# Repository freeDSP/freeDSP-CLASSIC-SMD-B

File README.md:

# freeDSP CLASSIC SMD

SMD update of the freeDSP CLASSIC.

**BOARD STATUS:** ✅ READY TO BE BUILT

## About

The freeDSP is an open-source digital signal processor family for the do-it-yourself community. The applications range from active loudspeaker concepts (digital crossovers, bass enhancement, ...) and room equalization over advanced musical effect processors to car audio signal processing.

This _freeDSP Classic SMD-B_ is a updated SMD version of the original _freeDSP Classic_ with a few improvements/changes.

This board has been designed using the Cross-Platform Open Source Tool [KiCad](http://kicad.org/).

More information can be found on the [freeDSP website](http://freedsp.cc)

You can find a PDF version of the schematic in the SOURCES folder (freeDSP_Classic_SMD.pdf)

## Links

### FreeDSP

Website: [http://freedsp.cc/](http://freedsp.cc)
FreeDSP Guidelines: [freedsp wiki - freeDSP-Guidelines](https://github.com/freeDSP/WIKI-AND-GENERAL-TOPICS/wiki/freeDSP-Guidelines)

### Documentation

[Getting Started (Google Doc)](https://docs.google.com/document/d/1K3joEg4iIRMazfqGLaVoBdybitr4o_KIVZfQ-qeNDzs/preview)  
[Getting Started (PDF Download)](https://docs.google.com/document/d/1K3joEg4iIRMazfqGLaVoBdybitr4o_KIVZfQ-qeNDzs/export?format=pdf)  

[Schematic (PDF)](./SOURCES/freeDSP_Classic_SMD.pdf)  
[Bill Of Materials (CSV)](./GERBER/freeDSP_Classic_SMD_BOM.csv)

## Git usage

### How to setup local repository

1. Change to your FreeDSP directory. This may be any directory you'd like to clone the repository to.
2. Clone the repository (including submodule)  
   `git clone --recursive https://github.com/freeDSP/freeDSP-CLASSIC-SMD-B.git`
3. Change to the newly created Classic-SMD-B directory
4. Checkout a branch for the library submodule, if you want to modify it as well  
   `git submodule foreach 'git checkout 'master''`
5. Open the project file in KiCad

**❔Note:** If you (accidentally) clone the repository without `--recursive`, initialise the `freeDSP/freeDSP-KiCadLibrary` submodule with `git submodule init ./LIBRARY`.

### Updating your local copy

1. To update the project  
   `git pull`
2. To update the library  
   `git submodule update --remote --merge`

### Committing and pushing local changes

This step requires you to have push access to the repository. If you do not have this, [create a fork](https://docs.github.com/en/get-started/quickstart/fork-a-repo#about-forks).

For ease of development, please use a separate branch (on your fork) to propose changes:

1. Create a new branch: git branch newfeature.
2. Checkout new branch: (this will not reset your work.) git checkout newfeature.

Then, continue to commit your changes:

1. If you modified something in the LIBRARY folder, change to the LIBRARY folder and run  
   `git add .` (Only required if files were added)  
   `git commit -am "Message"`  (Describe what you changed)  
2. Change to the project root directory and run
   `git add .` (Only required if files were added)  
   `git commit -am "Message"`  (Describe what you changed)  
3. In the project directory, run  
   `git push --recurse-submodule=on-demand`  

### Suggesting changes

To suggest changes from your fork and/or branch to [freeDSP][]/[freeDSP-CLASSIC-SMD-B][], follow the instructions that apply to you.

From a fork repository (outside contributors):

1. Navigate to the `Pull requests` page of your fork, and click "New pull request"
2. Review the changes in the differential below. Ideally, there are no merge conflicts, and you are "✅ Able to merge".  
   If you see no changes or differential, follow the steps outlined for the project contributors below.  
   if there are any merge conflicts, resolve these. See [Contributing to projects][docs-contrib] for more help.
3. Click "Create pull request" and enter
   - **Title** describing your suggestion briefly
   - **Comment** describing your suggestions one-by-one, or more in-depth
4. Click "Create pull request" once again. Your pull request will now be made.

From the main repository (for project contributors):

1. Navigate to the [pull requests][freedsp-pulls] page and click "New pull request"
2. Click "compare across forks" immediately below "Compare changes" if necessary.
3. Create a new pull request
   - select "master" as "base:"
   - select your branch on your fork as "compare:"
4. Review the changes in the differential below. Ideally, there are no merge conflicts, and you are "✅ Able to merge".  
   If there are any merge conflicts, resolve these. See [Contributing to projects][docs-contrib] for more help.
5. Click "Create pull request" and enter
   - **Title** describing your suggestion briefly
   - **Comment** describing your suggestions one-by-one, or more in-depth
6. Click "Create pull request" once again. Your pull request will now be made.

### Define alias to make things shorter (optional)

Change to the project root and run  

`git config alias.supdate 'submodule update --remote --merge'`  
`git config alias.spush 'push --recurse-submodules=on-demand'`  

Afterwards, you can use `git supdate` to update the submodule and `git spush` to push any commited changes  

### Other useful commands

`git status`  
Shows general information about the current branch, uncommited changes, not yet added new files and more

`git diff`  
Shows uncommited changes

`git reset --hard origin/master`  
Resets all files to the current status of the dev-hs-01 branch on the Github repository  
  **⚠️ Warning** - This deletes all local changes, so make sure all changes you made and you do not want to delete are pushed to the remote repository

## License

[Creative Commons Attribution Share-Alike 4.0 license](https://creativecommons.org/licenses/by-sa/4.0/)  
[Local license file](./LICENCE)

2019 ©️ [FreeDSP project](http://freedsp.cc)

[freeDSP]: https://github.com/freeDSP
[freeDSP-CLASSIC-SMD-B]: https://github.com/freeDSP/freeDSP-CLASSIC-SMD-B
[docs-contrib]:https://docs.github.com/en/get-started/quickstart/contributing-to-projects
[freedsp-pulls]:https://github.com/freeDSP/freeDSP-CLASSIC-SMD-B/pulls

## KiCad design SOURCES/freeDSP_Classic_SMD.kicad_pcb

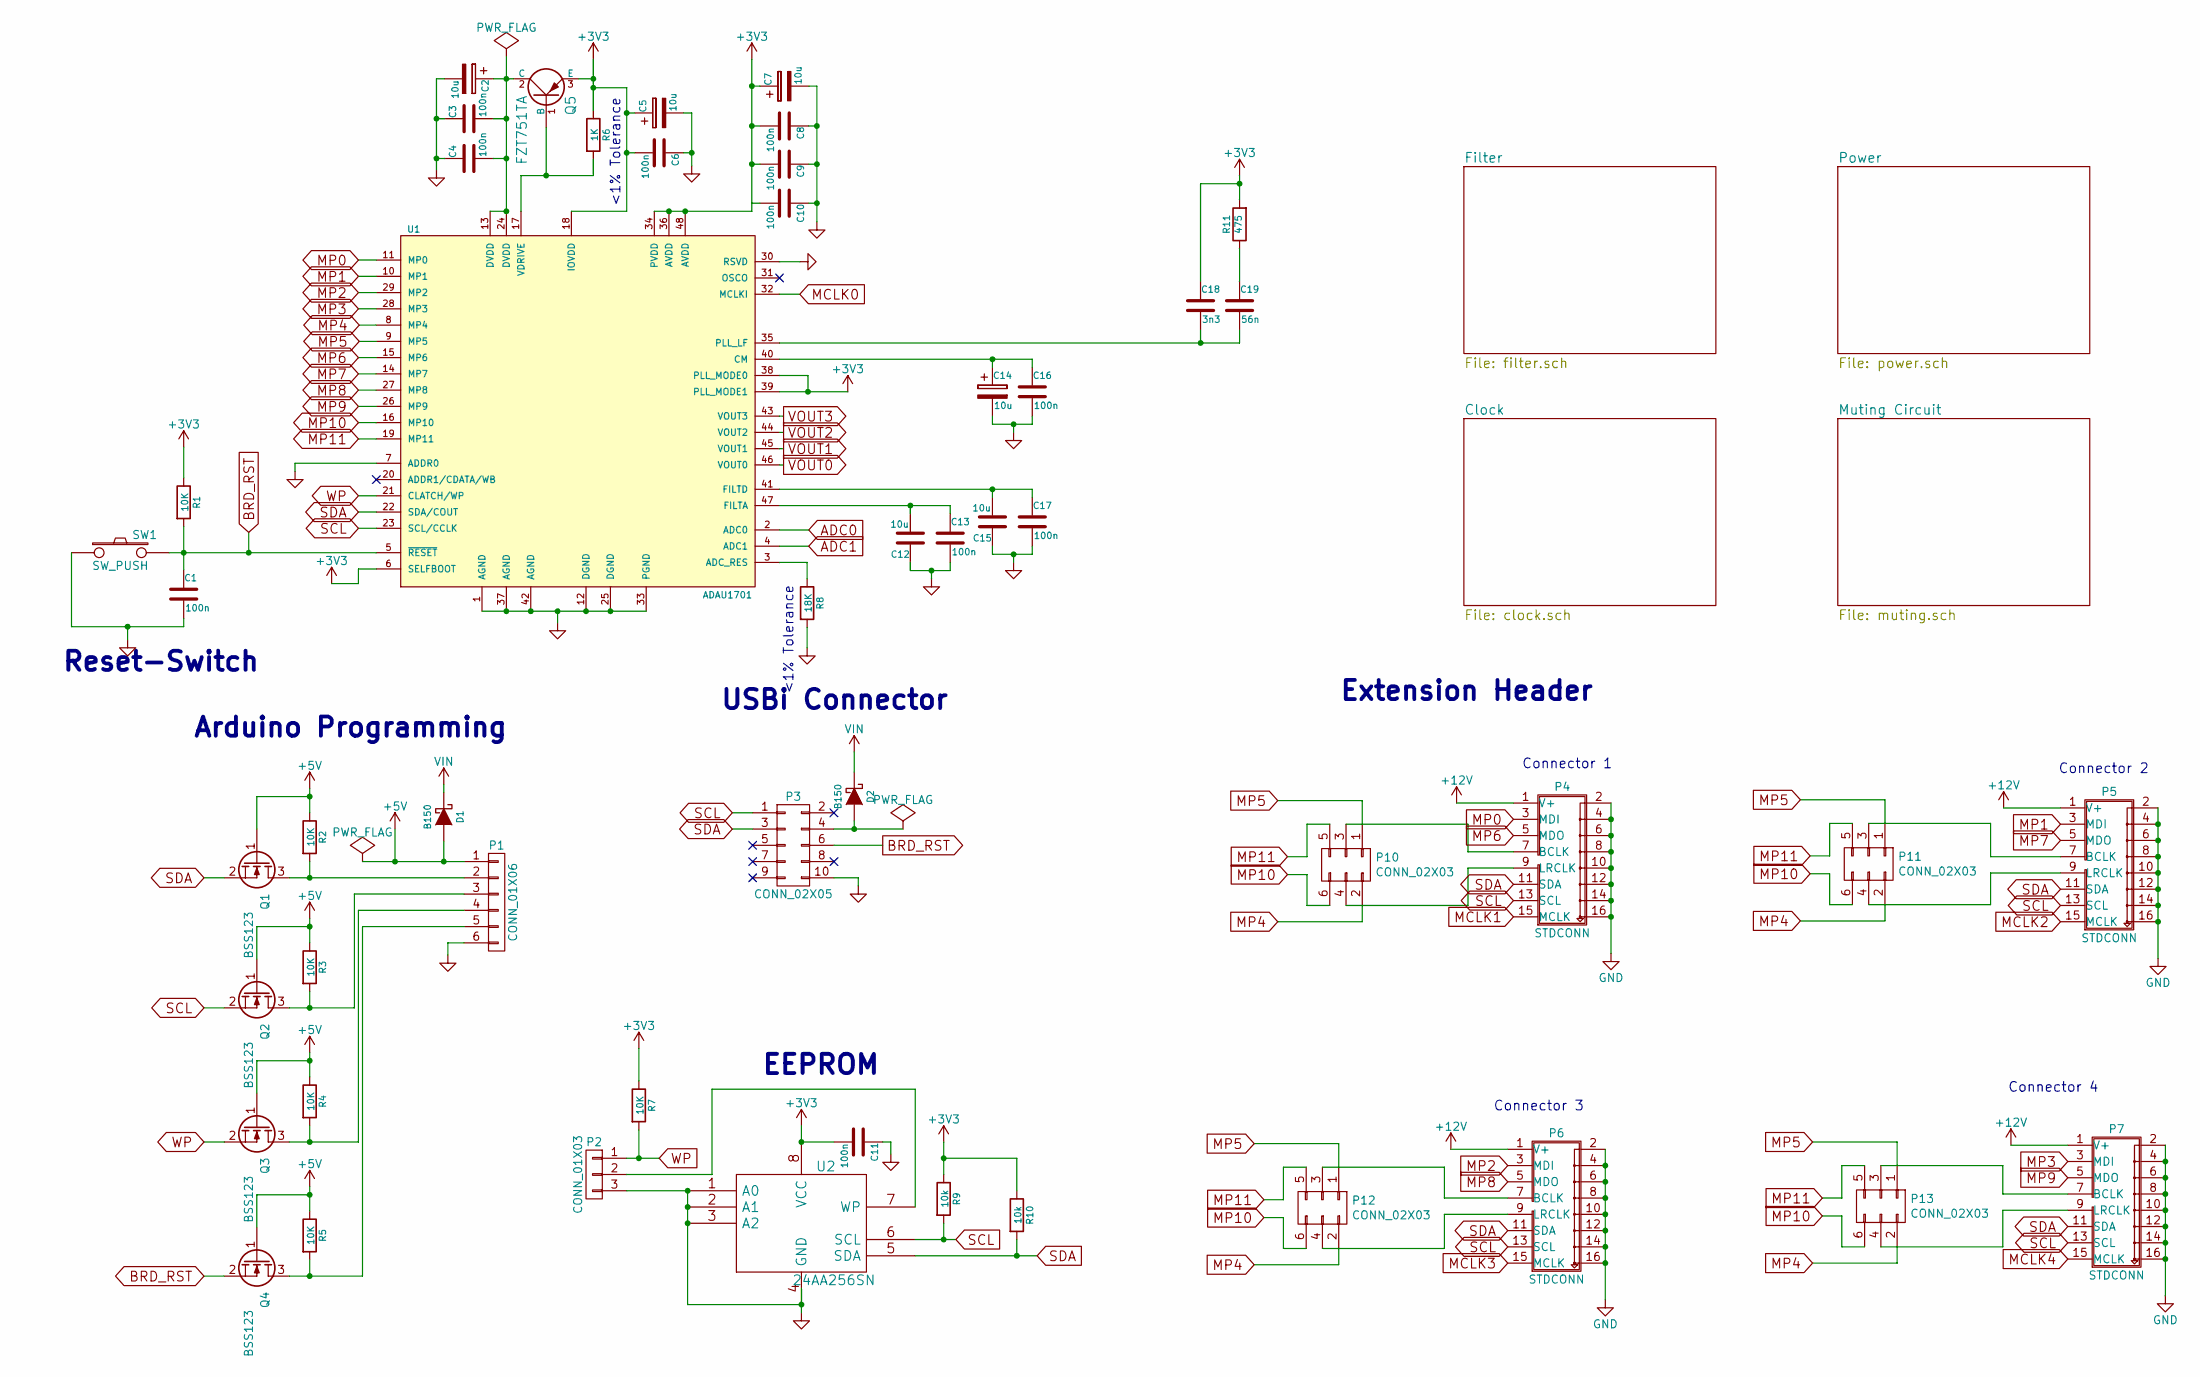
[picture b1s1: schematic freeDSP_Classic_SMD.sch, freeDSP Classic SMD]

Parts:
C1, C3, C4, C6, C8, C9, C10, C11, C13, C16, C17: 100n; C_1206_HandSoldering
C2, C5, C7, C14: 10u; C_Radial_D5_L11_P2
C12, C15: 10u; C_1206_HandSoldering
C18: 3n3; C_1206_HandSoldering
C19: 56n; C_1206_HandSoldering
D1, D2: B150; SMA
P1: CONN_01X06; Pin_Header_Straight_1x06
P2: CONN_01X03; Pin_Header_Straight_1x03
P3: CONN_02X05; IDC_Header_Straight_10pins
P4, P5, P6, P7: STDCONN; IDC_Header_Straight_16pins
P10, P11, P12, P13: CONN_02X03; Pin_Header_Straight_2x03
Q1, Q2, Q3, Q4: BSS123; SOT-23_Handsoldering
Q5: FZT751TA; SOT-223
R1, R2, R3, R4, R5, R7: 10K; R_1206_HandSoldering
R6: 1K; R_1206_HandSoldering
R8: 18K; R_1206_HandSoldering
R9, R10: 10k; R_1206_HandSoldering
R11: 475; R_1206_HandSoldering
SW1: SW_PUSH; SW_PUSH_6mm
U1: ADAU1701; LQFP-48_7x7mm_Pitch0.5mm
U2: 24AA256SN; SOIC-8_3.9x4.9mm_Pitch1.27mm

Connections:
+3V3: C5.1, C6.2, C7.1, C8.2, C9.2, C11.2, C18.1, Q5.3 (E), R1.1, R6.1, R7.1, R9.1, R10.1, R11.2, U1.6 (SELFBOOT), U1.18 (IOVDD), U1.34 (PVDD), U1.36 (AVDD), U1.38 (PLL_MODE0), U1.39 (PLL_MODE1), U1.48 (AVDD), U2.8 (VCC); also elsewhere on the board
+5V: D1.2 (A), P1.1, Q1.1 (G), Q2.1 (G), Q3.1 (G), Q4.1 (G), R2.1, R3.1, R4.1, R5.1
+12V: P4.1 (V+), P5.1 (V+), P6.1 (V+), P7.1 (V+); also elsewhere on the board
ADC0: U1.2 (ADC0); also elsewhere on the board
ADC1: U1.4 (ADC1); also elsewhere on the board
BRD_RST: C1.1, P3.6, Q4.2 (S), R1.2, SW1.2, U1.5 (~RESET~)
GND: C1.2, C2.2, C3.1, C4.1, C5.2, C6.1, C7.2, C8.1, C9.1, C10.1, C11.1, C12.1, C13.2, C14.2, C15.1, C16.2, C17.2, P1.6, P2.3, P3.10, P4.2 (GND), P4.4 (GND), P4.6 (GND), P4.8 (GND), P4.10 (GND), P4.12 (GND), P4.14 (GND), P4.16 (GND), P5.2 (GND), P5.4 (GND), P5.6 (GND), P5.8 (GND), P5.10 (GND), P5.12 (GND), P5.14 (GND), P5.16 (GND), P6.2 (GND), P6.4 (GND), P6.6 (GND), P6.8 (GND), P6.10 (GND), P6.12 (GND), P6.14 (GND), P6.16 (GND), P7.2 (GND), P7.4 (GND), P7.6 (GND), P7.8 (GND), P7.10 (GND), P7.12 (GND), P7.14 (GND), P7.16 (GND), R8.2, SW1.1, U1.1 (AGND), U1.7 (ADDR0), U1.12 (DGND), U1.25 (DGND), U1.30 (RSVD), U1.33 (PGND), U1.37 (AGND), U1.42 (AGND), U2.1 (A0), U2.2 (A1), U2.3 (A2), U2.4 (GND); also elsewhere on the board
MCLK0: U1.32 (MCLKI); also elsewhere on the board
MCLK1: P4.15 (MCLK); also elsewhere on the board
MCLK2: P5.15 (MCLK); also elsewhere on the board
MCLK3: P6.15 (MCLK); also elsewhere on the board
MCLK4: P7.15 (MCLK); also elsewhere on the board
MP0: P4.3 (MDI), U1.11 (MP0)
MP1: P5.3 (MDI), U1.10 (MP1)
MP2: P6.3 (MDI), U1.29 (MP2)
MP3: P7.3 (MDI), U1.28 (MP3)
MP4: P10.2, P11.2, P12.2, P13.2, U1.8 (MP4)
MP5: P10.1, P11.1, P12.1, P13.1, U1.9 (MP5)
MP6: P4.5 (MDO), U1.15 (MP6)
MP7: P5.5 (MDO), U1.14 (MP7)
MP8: P6.5 (MDO), U1.27 (MP8)
MP9: P7.5 (MDO), U1.26 (MP9)
MP10: P10.6, P11.6, P12.6, P13.6, U1.16 (MP10)
MP11: P10.5, P11.5, P12.5, P13.5, U1.19 (MP11)
unnamed: C2.1, C3.2, C4.2, Q5.2 (C), U1.13 (DVDD), U1.24 (DVDD)
unnamed: C12.2, C13.1, U1.47 (FILTA)
unnamed: C14.1, C16.1, U1.40 (CM)
unnamed: C15.2, C17.1, U1.41 (FILTD)
unnamed: C18.2, C19.2, U1.35 (PLL_LF)
unnamed: C19.1, R11.1
unnamed: D2.2 (A), P3.4
unnamed: P1.2, Q1.3 (D), R2.2
unnamed: P1.3, Q2.3 (D), R3.2
unnamed: P1.4, Q3.3 (D), R4.2
unnamed: P1.5, Q4.3 (D), R5.2
unnamed: P2.2, U2.7 (WP)
unnamed: P4.7 (BCLK), P10.3
unnamed: P4.9 (LRCLK), P10.4
unnamed: P5.7 (BCLK), P11.3
unnamed: P5.9 (LRCLK), P11.4
unnamed: P6.7 (BCLK), P12.3
unnamed: P6.9 (LRCLK), P12.4
unnamed: P7.7 (BCLK), P13.3
unnamed: P7.9 (LRCLK), P13.4
unnamed: Q5.1 (B), R6.2, U1.17 (VDRIVE)
unnamed: R8.1, U1.3 (ADC_RES)
SCL: P3.1, P4.13 (SCL), P5.13 (SCL), P6.13 (SCL), P7.13 (SCL), Q2.2 (S), R9.2, U1.23 (SCL/CCLK), U2.6 (SCL)
SDA: P3.3, P4.11 (SDA), P5.11 (SDA), P6.11 (SDA), P7.11 (SDA), Q1.2 (S), R10.2, U1.22 (SDA/COUT), U2.5 (SDA)
VIN: D1.1 (K), D2.1 (K); also elsewhere on the board
VOUT0: U1.46 (VOUT0); also elsewhere on the board
VOUT1: U1.45 (VOUT1); also elsewhere on the board
VOUT2: U1.44 (VOUT2); also elsewhere on the board
VOUT3: U1.43 (VOUT3); also elsewhere on the board
WP: P2.1, Q3.2 (S), R7.2, U1.21 (CLATCH/WP)

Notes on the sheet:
Reset-Switch
<1% Tolerance
EEPROM
USBi Connector
Arduino Programming
Extension Header
Connector 2
Connector 3
Connector 4
Connector 1

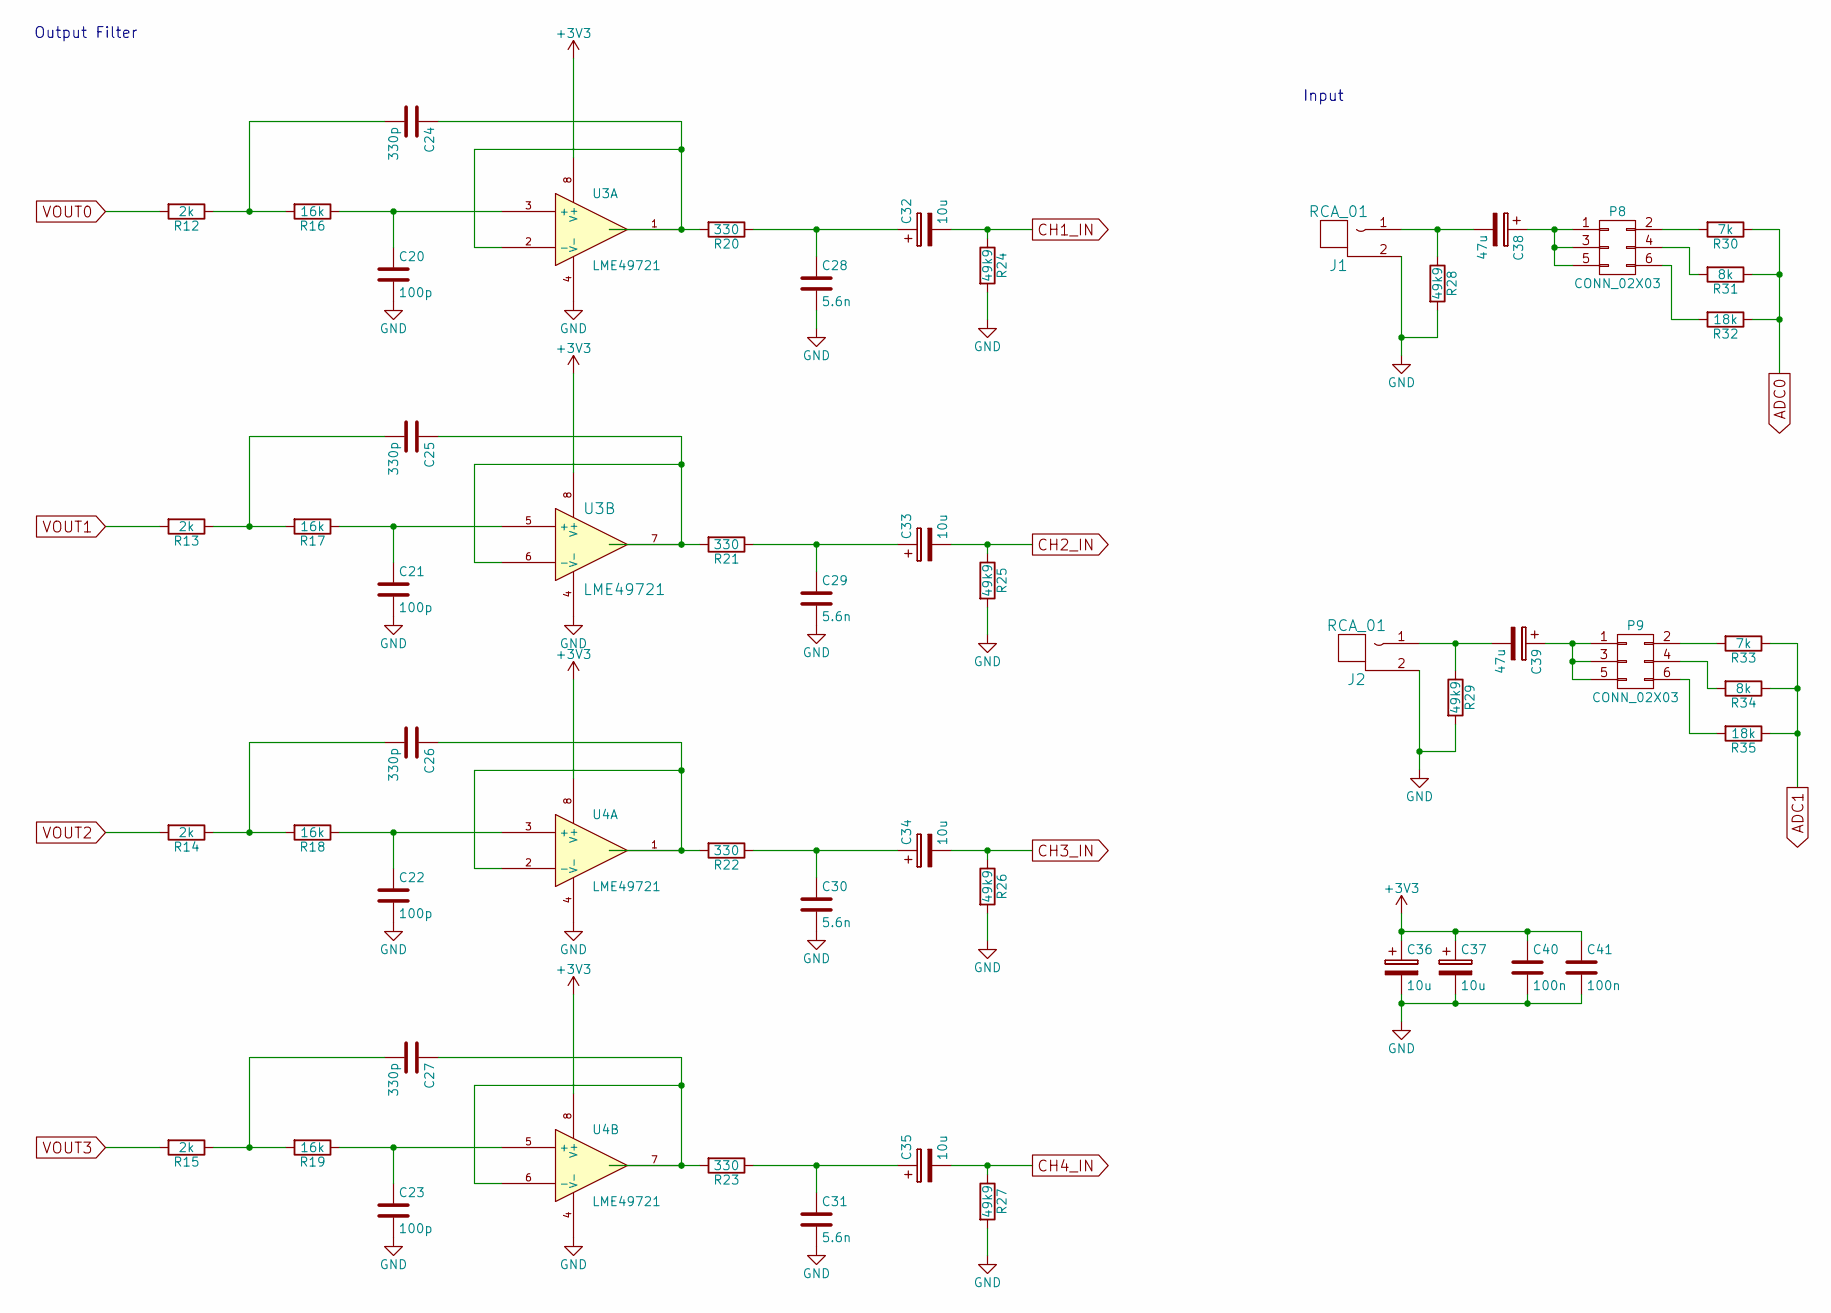
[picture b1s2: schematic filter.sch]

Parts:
C20, C21, C22, C23: 100p; C_1206_HandSoldering
C24, C25, C26, C27: 330p; C_1206_HandSoldering
C28, C29, C30, C31: 5.6n; C_1206_HandSoldering
C32, C33, C34, C35, C36, C37: 10u; C_Radial_D5_L11_P2
C38, C39: 47u; C_Radial_D5_L11_P2
C40, C41: 100n; C_1206_HandSoldering
J1, J2: RCA_01; RCA_RCJ-01x
P8, P9: CONN_02X03; Pin_Header_Straight_2x03
R12, R13, R14, R15: 2k; R_1206_HandSoldering
R16, R17, R18, R19: 16k; R_1206_HandSoldering
R20, R21, R22, R23: 330; R_1206_HandSoldering
R24, R25, R26, R27, R28, R29: 49k9; R_1206_HandSoldering
R30, R33: 7k; R_1206_HandSoldering
R31, R34: 8k; R_1206_HandSoldering
R32, R35: 18k; R_1206_HandSoldering
U3, U4: LME49721; SOIC-8_3.9x4.9mm_Pitch1.27mm

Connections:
+3V3: C36.1, C37.1, C40.1, C41.1, U3.8 (V+), U4.8 (V+); also elsewhere on the board
ADC0: R30.1, R31.1, R32.1; also elsewhere on the board
ADC1: R33.1, R34.1, R35.1; also elsewhere on the board
CH1_IN: C32.2, R24.1; also elsewhere on the board
CH2_IN: C33.2, R25.1; also elsewhere on the board
CH3_IN: C34.2, R26.1; also elsewhere on the board
CH4_IN: C35.2, R27.1; also elsewhere on the board
GND: C20.2, C21.2, C22.2, C23.2, C28.2, C29.2, C30.2, C31.2, C36.2, C37.2, C40.2, C41.2, J1.2 (GND), J2.2 (GND), R24.2, R25.2, R26.2, R27.2, R28.2, R29.2, U3.4 (V-), U4.4 (V-); also elsewhere on the board
unnamed: C20.1, R16.1, U3.3 (+)
unnamed: C21.1, R17.1, U3.5 (+)
unnamed: C22.1, R18.1, U4.3 (+)
unnamed: C23.1, R19.1, U4.5 (+)
unnamed: C24.1, R20.2, U3.1, U3.2 (-)
unnamed: C24.2, R12.1, R16.2
unnamed: C25.1, R21.2, U3.6 (-), U3.7
unnamed: C25.2, R13.1, R17.2
unnamed: C26.1, R22.2, U4.1, U4.2 (-)
unnamed: C26.2, R14.1, R18.2
unnamed: C27.1, R23.2, U4.6 (-), U4.7
unnamed: C27.2, R15.1, R19.2
unnamed: C28.1, C32.1, R20.1
unnamed: C29.1, C33.1, R21.1
unnamed: C30.1, C34.1, R22.1
unnamed: C31.1, C35.1, R23.1
unnamed: C38.1, P8.1, P8.3, P8.5
unnamed: C38.2, J1.1 (SIG), R28.1
unnamed: C39.1, P9.1, P9.3, P9.5
unnamed: C39.2, J2.1 (SIG), R29.1
unnamed: P8.2, R30.2
unnamed: P8.4, R31.2
unnamed: P8.6, R32.2
unnamed: P9.2, R33.2
unnamed: P9.4, R34.2
unnamed: P9.6, R35.2
VOUT0: R12.2; also elsewhere on the board
VOUT1: R13.2; also elsewhere on the board
VOUT2: R14.2; also elsewhere on the board
VOUT3: R15.2; also elsewhere on the board

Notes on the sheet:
Output Filter
Input

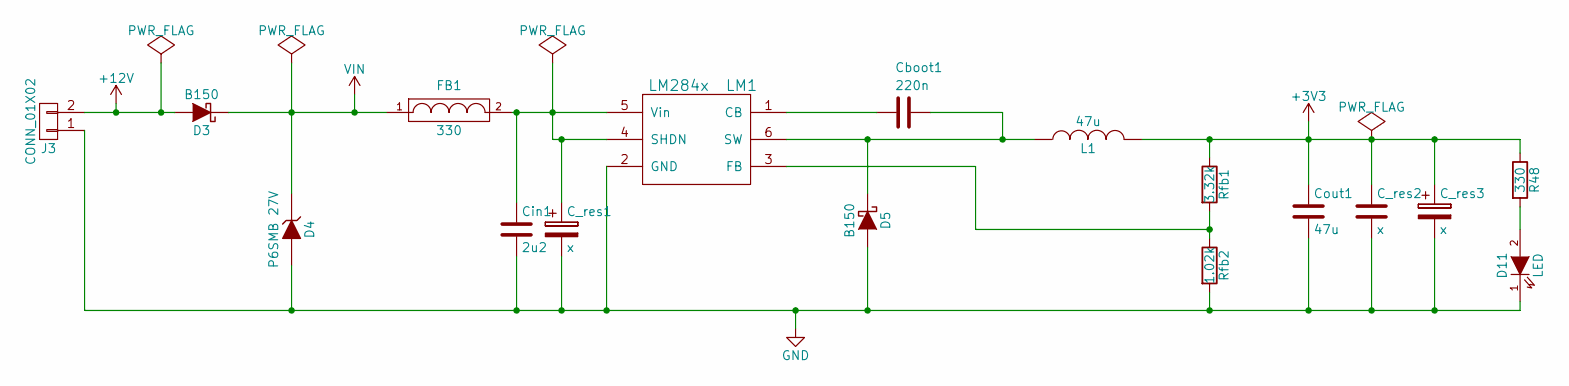
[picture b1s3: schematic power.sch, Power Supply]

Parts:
C_res1, C_res3: x; C_Radial_D5_L11_P2
C_res2: x; C_1206_HandSoldering
Cboot1: 220n; C_1206_HandSoldering
Cin1: 2u2; C_1206_HandSoldering
Cout1: 47u; C_1206_HandSoldering
D3, D5: B150; SMA
D4: P6SMB 27V; SMB
D11: LED; R_1206_HandSoldering
FB1: 330; C_0805_HandSoldering
J3: CONN_01X02; RIACON101-2
L1: 47u; Choke_SMD_6.0x5.8
LM1: LM284x; SOT23-6_1.7x3.0mm_Pitch0.95mm
R48: 330; R_1206_HandSoldering
Rfb1: 3.32k; R_1206_HandSoldering
Rfb2: 1.02k; R_1206_HandSoldering

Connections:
+3V3: C_res2.1, C_res3.1, Cout1.1, L1.2, R48.1, Rfb1.1; also elsewhere on the board
+12V: D3.2 (A), J3.2; also elsewhere on the board
GND: C_res1.2, C_res2.2, C_res3.2, Cin1.2, Cout1.2, D4.2 (A), D5.2 (A), D11.1 (K), J3.1, LM1.2 (GND), Rfb2.2; also elsewhere on the board
unnamed: C_res1.1, Cin1.1, FB1.2, LM1.4 (SHDN), LM1.5 (Vin)
unnamed: Cboot1.1, D5.1 (K), L1.1, LM1.6 (SW)
unnamed: Cboot1.2, LM1.1 (CB)
unnamed: D11.2 (A), R48.2
unnamed: LM1.3 (FB), Rfb1.2, Rfb2.1
VIN: D3.1 (K), D4.1 (K), FB1.1; also elsewhere on the board

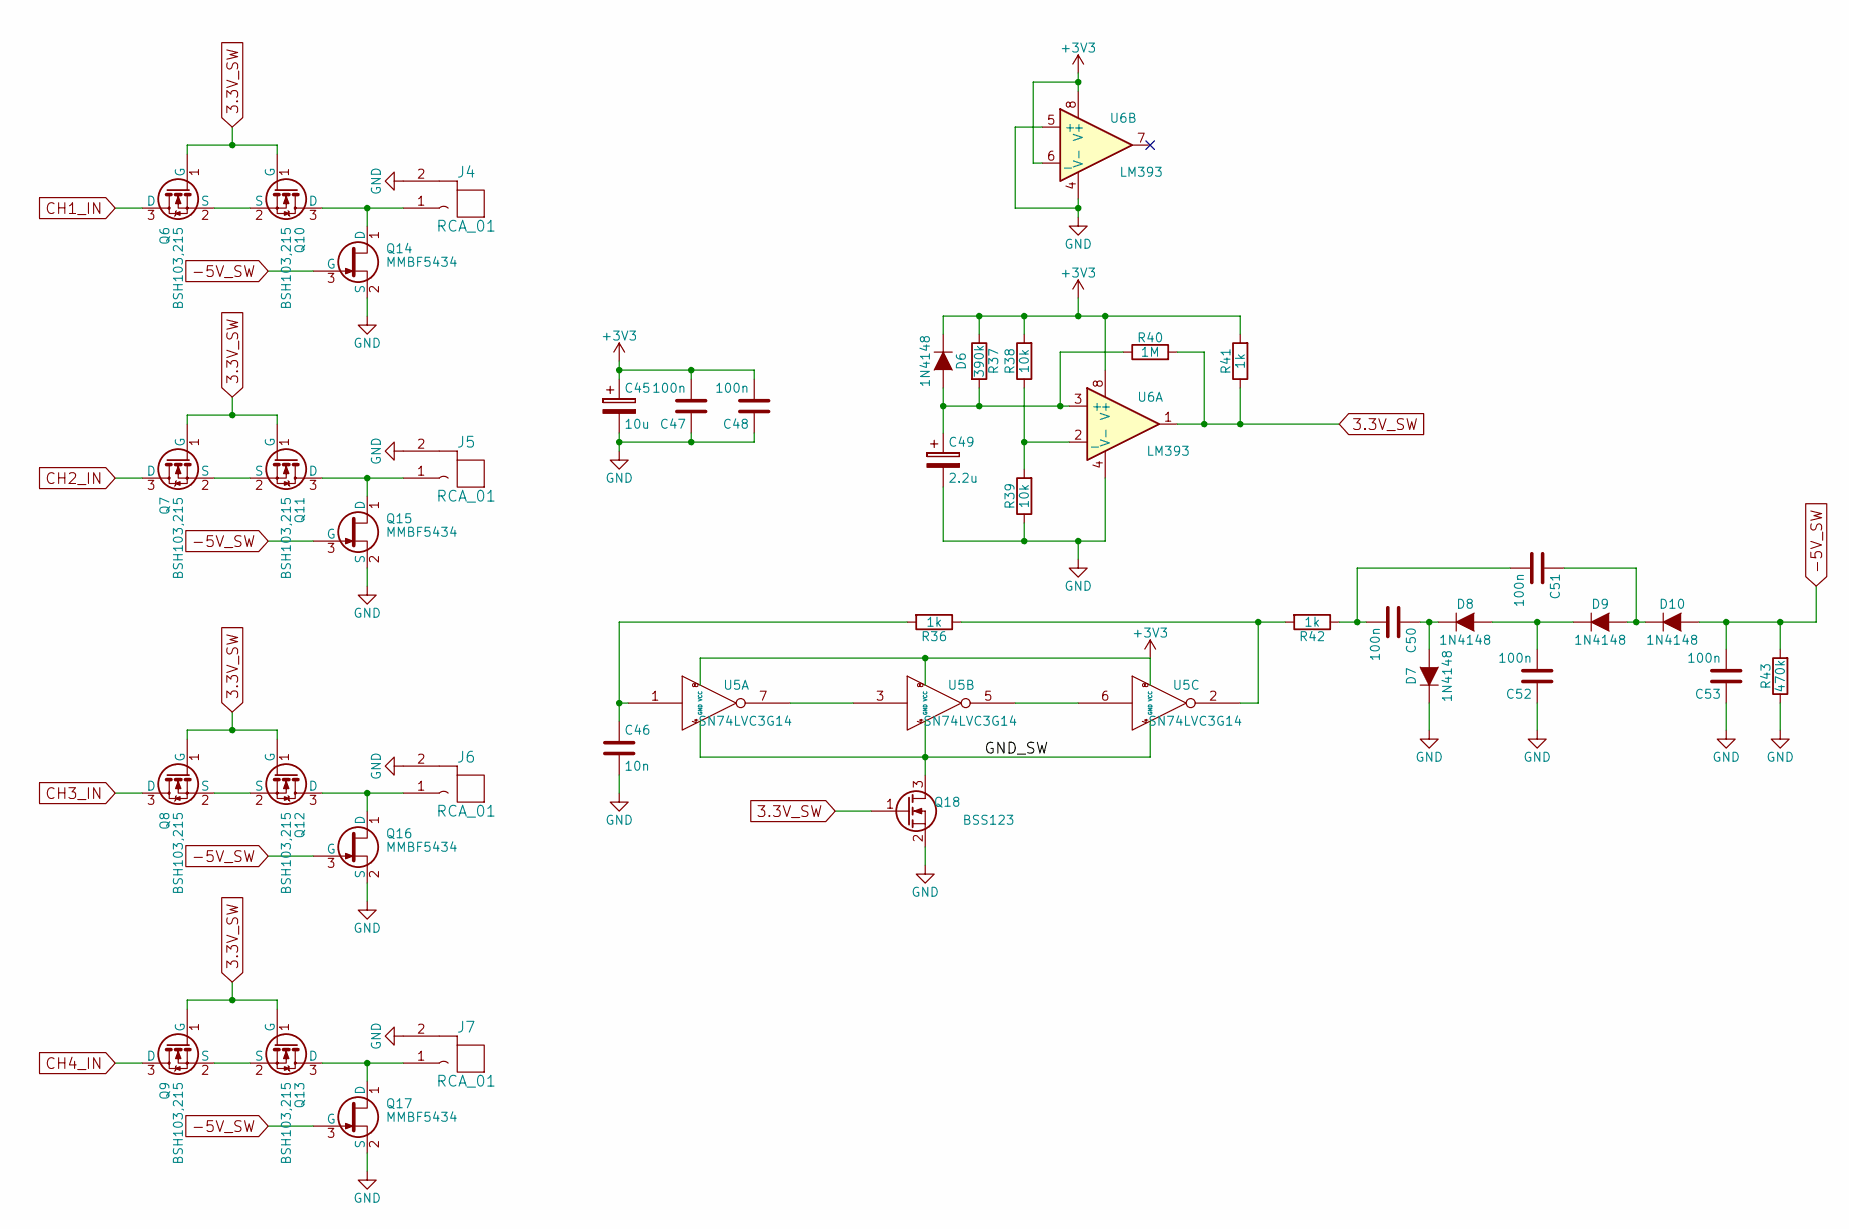
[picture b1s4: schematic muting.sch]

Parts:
C45: 10u; C_Radial_D5_L11_P2
C46: 10n; C_1206_HandSoldering
C47, C48, C50, C51, C52, C53: 100n; C_1206_HandSoldering
C49: 2.2u; C_Radial_D5_L11_P2
D6, D7, D8, D9, D10: 1N4148; SOD-123W
J4, J5, J6, J7: RCA_01; RCA_RCJ-01x
Q6, Q7, Q8, Q9, Q10, Q11, Q12, Q13: BSH103,215; SOT-23_Handsoldering
Q14, Q15, Q16, Q17: MMBF5434; SOT-23_Handsoldering
Q18: BSS123; SOT-23_Handsoldering
R36, R41, R42: 1k; R_1206_HandSoldering
R37: 390k; R_1206_HandSoldering
R38, R39: 10k; R_1206_HandSoldering
R40: 1M; R_1206_HandSoldering
R43: 470k; R_1206_HandSoldering
U5: SN74LVC3G14; DCT
U6: LM393; SOIC-8_3.9x4.9mm_Pitch1.27mm

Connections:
3.3V_SW: Q6.1 (G), Q7.1 (G), Q8.1 (G), Q9.1 (G), Q10.1 (G), Q11.1 (G), Q12.1 (G), Q13.1 (G), Q18.1 (G), R40.2, R41.1, U6.1
+3V3: C45.1, C47.2, C48.2, D6.1 (K), R37.1, R38.2, R41.2, U5.8 (VCC), U6.6 (_), U6.8 (V+); also elsewhere on the board
-5V_SW: C53.2, D10.2 (A), Q14.3 (G), Q15.3 (G), Q16.3 (G), Q17.3 (G), R43.2
/Muting Circuit/GND_SW: Q18.3 (D), U5.4 (GND)
CH1_IN: Q6.3 (D); also elsewhere on the board
CH2_IN: Q7.3 (D); also elsewhere on the board
CH3_IN: Q8.3 (D); also elsewhere on the board
CH4_IN: Q9.3 (D); also elsewhere on the board
GND: C45.2, C46.2, C47.1, C48.1, C49.2, C52.1, C53.1, D7.1 (K), J4.2 (GND), J5.2 (GND), J6.2 (GND), J7.2 (GND), Q14.2 (S), Q15.2 (S), Q16.2 (S), Q17.2 (S), Q18.2 (S), R39.1, R43.1, U6.4 (V-), U6.5 (+); also elsewhere on the board
unnamed: C46.1, R36.2, U5.1
unnamed: C49.1, D6.2 (A), R37.2, R40.1, U6.3 (+)
unnamed: C50.1, D7.2 (A), D8.1 (K)
unnamed: C50.2, C51.2, R42.1
unnamed: C51.1, D9.2 (A), D10.1 (K)
unnamed: C52.2, D8.2 (A), D9.1 (K)
unnamed: J4.1 (SIG), Q10.3 (D), Q14.1 (D)
unnamed: J5.1 (SIG), Q11.3 (D), Q15.1 (D)
unnamed: J6.1 (SIG), Q12.3 (D), Q16.1 (D)
unnamed: J7.1 (SIG), Q13.3 (D), Q17.1 (D)
unnamed: Q6.2 (S), Q10.2 (S)
unnamed: Q7.2 (S), Q11.2 (S)
unnamed: Q8.2 (S), Q12.2 (S)
unnamed: Q9.2 (S), Q13.2 (S)
unnamed: R36.1, R42.2, U5.2
unnamed: R38.1, R39.2, U6.2 (_)
unnamed: U5.3, U5.7
unnamed: U5.5, U5.6

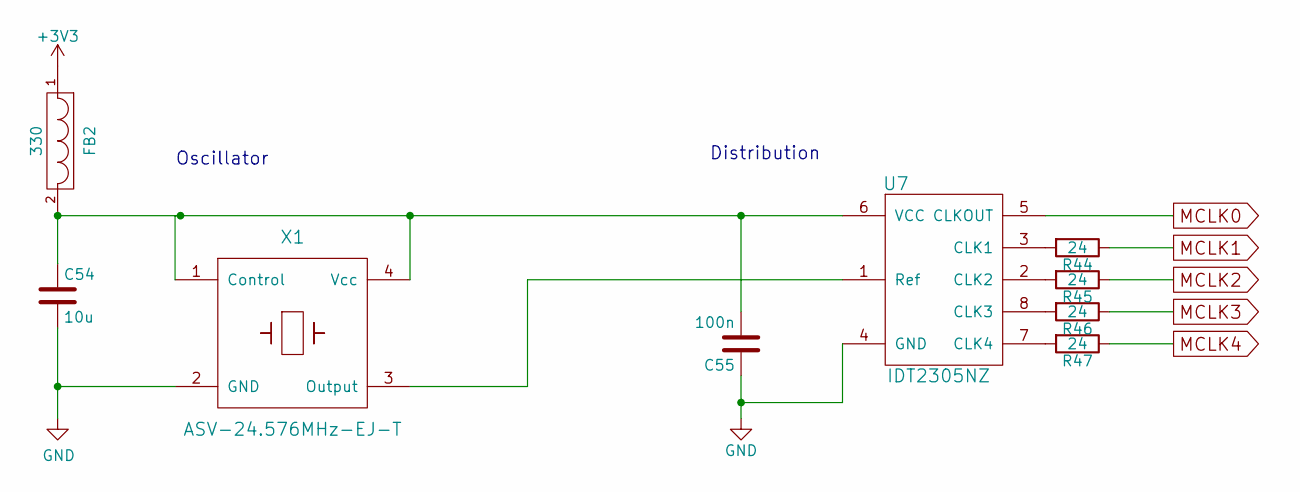
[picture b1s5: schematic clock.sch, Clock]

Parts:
C54: 10u; C_1206_HandSoldering
C55: 100n; C_1206_HandSoldering
FB2: 330; C_0805_HandSoldering
R44, R45, R46, R47: 24; R_1206_HandSoldering
U7: IDT2305NZ; SOIC-8_3.9x4.9mm_Pitch1.27mm
X1: ASV-24.576MHz-EJ-T; Oscillator_SMD_Abracon_ASV-4pin_7.0x5.1mm_HandSoldering

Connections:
+3V3: FB2.1; also elsewhere on the board
GND: C54.2, C55.1, U7.4 (GND), X1.2 (GND); also elsewhere on the board
MCLK0: U7.5 (CLKOUT); also elsewhere on the board
MCLK1: R44.1; also elsewhere on the board
MCLK2: R45.1; also elsewhere on the board
MCLK3: R46.1; also elsewhere on the board
MCLK4: R47.1; also elsewhere on the board
unnamed: C54.1, C55.2, FB2.2, U7.6 (VCC), X1.1 (Control), X1.4 (Vcc)
unnamed: R44.2, U7.3 (CLK1)
unnamed: R45.2, U7.2 (CLK2)
unnamed: R46.2, U7.8 (CLK3)
unnamed: R47.2, U7.7 (CLK4)
unnamed: U7.1 (Ref), X1.3 (Output)

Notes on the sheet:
Oscillator
Distribution

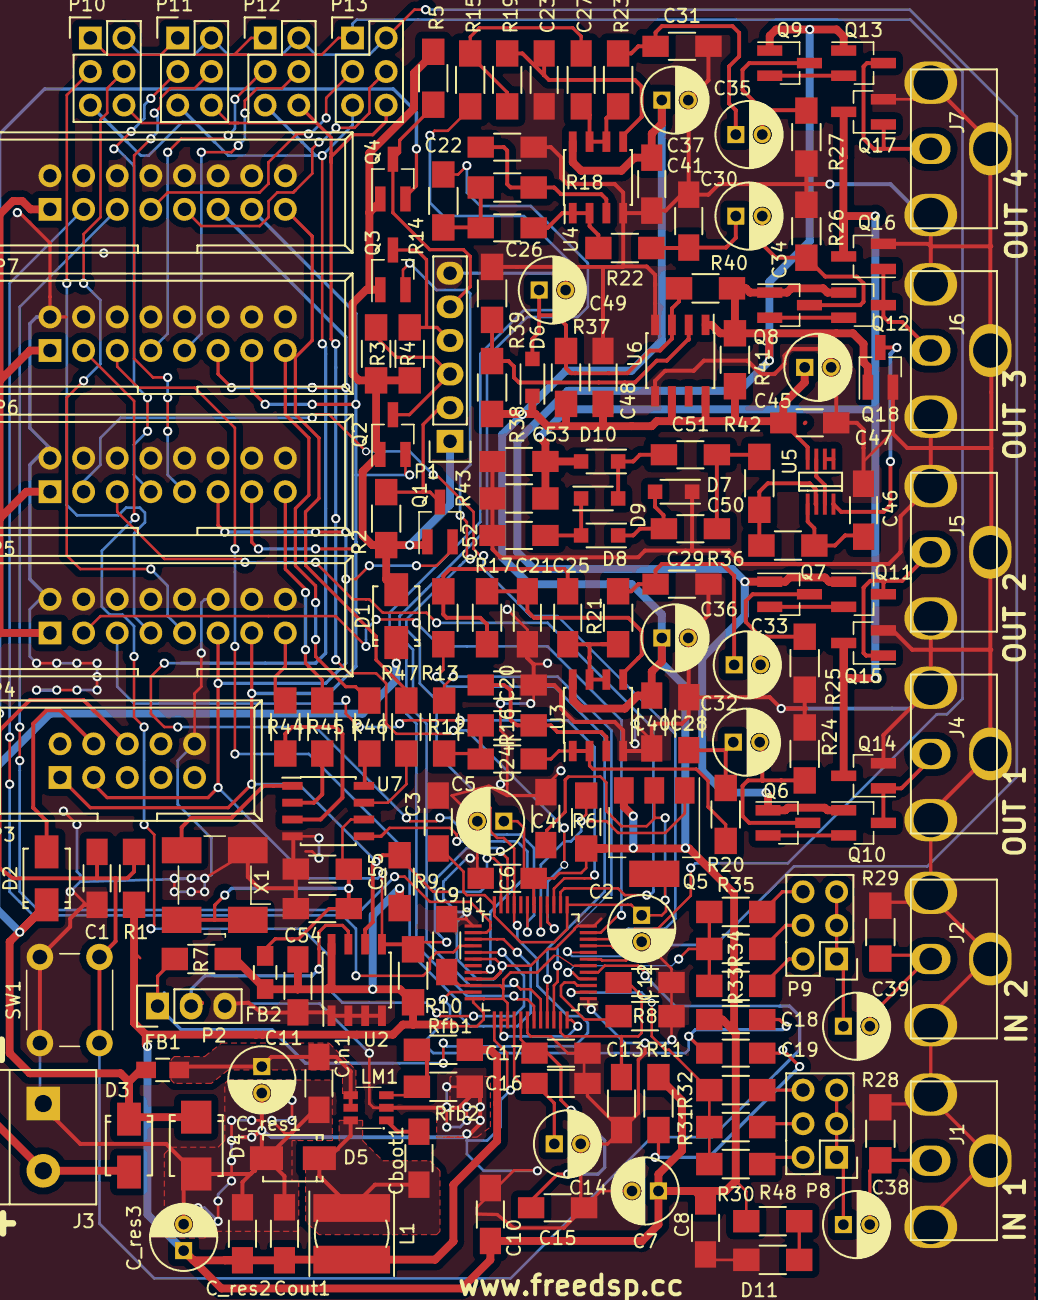
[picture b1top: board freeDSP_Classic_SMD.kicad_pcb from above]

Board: 2 copper layers, 170 parts (0 on the bottom side), 116 nets.

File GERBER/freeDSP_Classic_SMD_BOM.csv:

"ID";"Bezeichner";"Gehäuse";"Stückzahl";"Bezeichnung";"Anbieter und Referenz";
1;"P7,P4,P6,P5";"IDC_Header_Straight_16pins";4;"STDCONN";;;
2;"P12,P10,P11,P13";"Pin_Header_Straight_2x03";4;"CONN_02X03";;;
3;"P3";"IDC_Header_Straight_10pins";1;"CONN_02X05";;;
4;"C1,C3,C4,C6,C8,C9,C10,C11,C13,C16,C17,C40,C41,C47,C48,C50,C51,C52,C53,C55";"C_1206_HandSoldering";20;"100n";;;
5;"C12,C15,C54";"C_1206_HandSoldering";3;"10u";;;
6;"C18";"C_1206_HandSoldering";1;"3n3";;;
7;"C19";"C_1206_HandSoldering";1;"56n";;;
8;"C20,C21,C22,C23";"C_1206_HandSoldering";4;"100p";;;
9;"C24,C25,C26,C27";"C_1206_HandSoldering";4;"330p";;;
10;"C28,C29,C30,C31";"C_1206_HandSoldering";4;"5.6n";;;
11;"C32,C33,C34,C35,C36,C37,C45,C2,C5,C7,C14";"C_Radial_D5_L11_P2";11;"10u";;;
12;"C38,C39";"C_Radial_D5_L11_P2";2;"47u";;;
13;"C46";"C_1206_HandSoldering";1;"10n";;;
14;"C49";"C_Radial_D5_L11_P2";1;"2.2u";;;
15;"Cboot1";"C_1206_HandSoldering";1;"220n";;;
16;"Cin1";"C_1206_HandSoldering";1;"2u2";;;
17;"Cout1";"C_1206_HandSoldering";1;"47u";;;
18;"C_res1,C_res3";"C_Radial_D5_L11_P2";2;"x";;;
19;"C_res2";"C_1206_HandSoldering";1;"x";;;
20;"D1,D2,D3,D5";"SMA";4;"B150";;;
21;"D4";"SMB";1;"P6SMB 27V";;;
22;"D6,D7,D8,D9,D10";"SOD-123W";5;"1N4148";;;
23;"FB1,FB2";"C_0805_HandSoldering";2;"330";;;
24;"J1,J2,J4,J5,J6,J7";"RCA_RCJ-01x";6;"RCA_01";;;
25;"J3";"RIACON101-2";1;"CONN_01X02";;;
26;"L1";"Choke_SMD_6.0x5.8";1;"47u";;;
27;"LM1";"SOT23-6_1.7x3.0mm_Pitch0.95mm";1;"LM284x";;;
28;"P1";"Pin_Header_Straight_1x06";1;"CONN_01X06";;;
29;"P2";"Pin_Header_Straight_1x03";1;"CONN_01X03";;;
30;"P8,P9";"Pin_Header_Straight_2x03";2;"CONN_02X03";;;
31;"R1,R2,R3,R4,R5,R7";"R_1206_HandSoldering";6;"10K";;;
32;"R6";"R_1206_HandSoldering";1;"1K";;;
33;"R8";"R_1206_HandSoldering";1;"18K";;;
34;"R9,R10,R38,R39";"R_1206_HandSoldering";4;"10k";;;
35;"R11";"R_1206_HandSoldering";1;"475";;;
36;"R12,R13,R14,R15";"R_1206_HandSoldering";4;"2k";;;
37;"R16,R17,R18,R19";"R_1206_HandSoldering";4;"16k";;;
38;"R20,R21,R22,R23,R48";"R_1206_HandSoldering";5;"330";;;
39;"R24,R25,R26,R27,R28,R29";"R_1206_HandSoldering";6;"49k9";;;
40;"R30,R33";"R_1206_HandSoldering";2;"7k";;;
41;"R31,R34";"R_1206_HandSoldering";2;"8k";;;
42;"R32,R35";"R_1206_HandSoldering";2;"18k";;;
43;"R36,R41,R42";"R_1206_HandSoldering";3;"1k";;;
44;"R37";"R_1206_HandSoldering";1;"390k";;;
45;"R40";"R_1206_HandSoldering";1;"1M";;;
46;"R43";"R_1206_HandSoldering";1;"470k";;;
47;"R44,R45,R46,R47";"R_1206_HandSoldering";4;"24";;;
48;"Rfb1";"R_1206_HandSoldering";1;"3.32k";;;
49;"Rfb2";"R_1206_HandSoldering";1;"1.02k";;;
50;"U1";"LQFP-48_7x7mm_Pitch0.5mm";1;"ADAU1701";;;
51;"U2";"SOIC-8_3.9x4.9mm_Pitch1.27mm";1;"24AA256SN";;;
52;"U3,U4";"SOIC-8_3.9x4.9mm_Pitch1.27mm";2;"LME49721";;;
53;"U5";"DCT";1;"SN74LVC3G14";;;
54;"U6";"SOIC-8_3.9x4.9mm_Pitch1.27mm";1;"LM393";;;
55;"U7";"SOIC-8_3.9x4.9mm_Pitch1.27mm";1;"IDT2305NZ";;;
56;"X1";"Oscillator_SMD_Abracon_ASV-4pin_7.0x5.1mm_HandSoldering";1;"ASV-24.576MHz-EJ-T";;;
57;"Q1,Q2,Q3,Q4,Q18";"SOT-23_Handsoldering";5;"BSS123";;;
58;"Q6,Q7,Q8,Q9,Q10,Q11,Q12,Q13";"SOT-23_Handsoldering";8;"BSH103,215";;;
59;"Q14,Q15,Q16,Q17";"SOT-23_Handsoldering";4;"MMBF5434";;;
60;"SW1";"SW_PUSH_6mm";1;"SW_PUSH";;;
61;"D11";"R_1206_HandSoldering";1;"LED";;;
62;"Q5";"SOT-223";1;"FZT751TA";;;

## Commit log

2016-06-15 General Update
    * added fdsp-libraries
    * redid all missing connections (update to kicad4 standard-parts)
2016-07-16 * finished filter schematics, fixed some missing connections
    * next up: power supply
2017-05-03 Added Library as submodule
2017-05-03 Switched to relative library paths
2017-05-03 Added short git description to README
2017-05-03 Updated Library Module
2017-05-03 Updated folder structure
2017-05-03 Fixed typo
2017-05-03 test
2017-05-05 Added LM284x Documentation
2017-05-15 Update simulations
2017-05-15 Added some LM2841x simulation
2017-05-16 add muting-circuit simulation files
2017-05-16 clock added
2017-05-17 part value options
2017-05-17 Add KiCad schematic for muting circuit
2017-05-22 Added LMR14203 Dokumentation
2017-05-22 Updated muting schematics
2017-05-28 Updated clock schematic and added footprints
2017-05-28 Added schematics and more for power regulator
2017-05-28 Added connector to power supply
2017-05-29 filter update
2017-05-29 Updated schematics and added subcircuits to main sheet
2017-05-29 Updated schematics
2017-05-29 Simulations update
2017-05-29 exchanged clock driver
2017-05-30 marker
2017-05-30 Updated schematics and labels
2017-05-30 Assigned footprints
2017-05-30 Create LICENCE
2017-05-30 Add measurements for muting circuit
2017-05-31 Added new footprints
2017-05-31 updated schematic + bom + pcb start
2017-05-31 layout: placed some components
2017-05-31 updated pcb
2017-06-01 pcb update
2017-06-01 Filters and Muting Circuit routed
2017-06-02 fixed switched GND Q18, placed some components
2017-06-06 further routing
2017-06-06 layout finished
2017-06-07 added logos and gnd vias, generated gerber files
2017-06-07 improved layout
2017-06-07 added schematic as pdf
2017-06-08 layout improvements
2017-06-11 added fiducials
2017-06-12 some improvements
2017-06-12 corrected fiducials
2017-06-12 uploaded new GERBER files
2017-06-16 corrected silkscreen, added schematic information
2017-07-05 added power led, changed via drill size
2017-07-05 corrected a wire, updated GERBER
2017-07-13 changed filter resistors, clock resistors
2017-07-15 Termination resistors changed to 24Ohms
2017-08-08 Added datasheet for lme49721
2017-08-13 fixed wrong pinouts added some text
2017-08-13 Modified FZT751
2017-08-13 Modified FZT751 Part2
2017-08-13 Moved ADAU to correct library
2017-08-13 Removed rescue lib
2017-08-13 Updated Library
2017-08-16 Fixed missing rescue library
2017-08-16 corrected some things in layout and schematic
2017-08-17 Removed unnecessary rescue lib
2017-08-17 Removed duplicate ADAU
2017-08-21 updated GERBER files
2017-08-23 Updated submodule to standard library and uploaded new schematics
2017-09-26 Update board status to 'READY TO BE BUILT'
2017-09-27 Updated links and description in README
2017-09-27 Added a description
2019-04-09 Added I2S-Solution
    Jumper für I2S Lösung hinzugefügt.
    Allerdings musste der, in den Design Rules vorgegebene Seitenabstand eingebüßt werden.
2019-04-19 Revision Completion
    Refreshed GERBER and other manufacturing data.
    - new GEERBER
    - new schematic
    - new drill; BOM; etc.
2021-11-08 Update README.md
    https://forum.kicad.info/t/warning-avoid-all-links-to-kicad-pcb-org-use-kicad-org/31521
2022-12-19 Readme changes
